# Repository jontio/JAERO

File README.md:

# JAERO

A SatCom ACARS demodulator and decoder for the Aero standard written in C++ Qt

This program demodulates and decodes ACARS messages sent from satellites to Aeroplanes (SatCom ACARS) commonly used when Aeroplanes are beyond VHF range. Demodulation is performed using the soundcard.
Such signals are typically around 1.5Ghz and can be received with a simple low gain antenna that can be home brewed in a few hours in conjunction with a cheap [RTL-SDR] dongle.

The 600 and 1200 bps SatCom ACARS signals are basically MSK like so the demodulator was forked from [JMSK]. The demodulator implements a coherent MSK demodulator type as seen at http://jontio.zapto.org/hda1/msk-demodulation2.html.

The 600 and 1200 bps demodulator uses the technique that treats the signal similar to [OQPSK] but with sine wave transitions rather than rectangular transitions. The BER (*Bit Error Rate*) versus EbNo (*Energy per bit to Noise power density*) performance in the presence of AWGN (*Additive White Gaussian Noise*) is the same as coherently demodulated differentially encoded [BPSK]. While designed for MSK it will also demodulate [GMSK] and some types of [BPSK]. The signal is supplied via the audio input of the computer’s soundcard.
The software implements differential decoding hence the modulator must use differential encoding. The output of the demodulator can be directed to either a built-in console or to a [UDP] network port.

An OQPSK demodulator was added and supports the faster 8400bps and 10.5k Aero signals.

Both 1200 and 10.5k burst C-band signal demodulation (From plane to ground station) are supported.

C-Channel signals at 8400bps that are for voice can be demodulated.

## Binaries

Precompiled binaries can be downloaded from [Releases].

## Directory structure

The [JAERO](JAERO) directory is where the Qt pro file is for the main application. The [udptextserver](udptextserver) directory is a small demo application for receiving data sent from JAERO.

## Compiling JAERO

Compiling JAERO requires the Qt framework. I would suggest using [MSYS2] to install the Qt framework and the rest of the development environment. Qt Creator can be used to compile JAERO and comes with the Qt framework. At least version 5 of the Qt framework is required. I only use MinGW and GCC for building so don't know if MSVC works.

I've now added Windows and Linux build scripts. The Windows build script requires MSYS2, once installed run msys64 clone the repo then type `./ci-windows-build.sh`. The Linux build script is for Debian based distros and will need to be changed for others; I have only tested it on some of the Ubuntu family (Ubuntu, Kubuntu and Lubuntu). For Linux type `./ci-linux-build.sh`, it will install JAERO as a few packages so uninstalling should be clean. For Windows there is no fancy installer but rather just a folder with the dependencies and the exe file itself. The build will fail if any of the dependency folders already exist; so the scripts could still do with a bit more work. Currently the aim of the scripts is as a way of automatically building JAERO from a default system so I can easily make changes to the code and not have the hassle of build releases.

I've added a continuous integration script [.github/workflows/ci-windows-build.yml](.github/workflows/ci-windows-build.yml) that will get Gihub to build JAERO for both Windows and Ubuntu. Currently the script is triggered manually in the [actions](https://github.com/jontio/JAERO/actions) tab. I suspect some older computers, say ones that don't support AVX instructions may now not run the new releases created in this manor and will need building on the intended computer itself.

JAERO's dependencies will undoubtedly change over time, so I suspect eventually the build scripts will fail and will need fixing. Till then they work, but I have no idea how long they will work for.

## Thanks

I'd like to thank everyone who has given their kind support for JAERO over the years. Thanks for Otti for getting the project started, John and Bev for setting up a worldwide large dish network, everyone who has donated, the people who have send feedback, people who use JAERO, Jeroen who done an excellent job programming new code for JAERO to bring some features that I’m sure will be appreciated by many, Tomasz for adding more ACARS message support, Corrosive for adding documentation, and the many other people who have written the libraries that JAERO uses.

Jonti 2021
<br>
https://jontio.zapto.org

[OQPSK]: https://en.wikipedia.org/wiki/Phase-shift_keying#Offset_QPSK_.28OQPSK.29
[GMSK]: https://en.wikipedia.org/wiki/Minimum-shift_keying#Gaussian_minimum-shift_keying
[BPSK]: https://en.wikipedia.org/wiki/Phase-shift_keying#Binary_phase-shift_keying_.28BPSK.29
[UDP]: https://en.wikipedia.org/wiki/User_Datagram_Protocol
[SSB]: https://en.wikipedia.org/wiki/Single-sideband_modulation
[Arduino]: https://www.arduino.cc/
[Varicode]: https://en.wikipedia.org/wiki/Varicode
[Spectrum Lab]: http://www.qsl.net/dl4yhf/spectra1.html
[JMSK]: https://github.com/jontio/JMSK
[RTL-SDR]: http://www.rtl-sdr.com/about-rtl-sdr/
[Releases]: https://github.com/jontio/JAERO/releases
[JAERO Wiki]: https://github.com/jontio/JAERO/wiki
[MSYS2]: https://www.msys2.org/

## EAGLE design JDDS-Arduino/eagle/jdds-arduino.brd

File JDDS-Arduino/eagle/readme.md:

Made with Eagle 7.4.0 Lite. (Free version)

These files show the default conntections for the JDDS-Arduino and a posible shield for an Arduino Uno.

With [Eagle PCB software](http://www.cadsoftusa.com/) You can modify the schematic and PCB to suit your needs.

Schematic of the connections

Possible shield for the Arduino Uno

Jonti

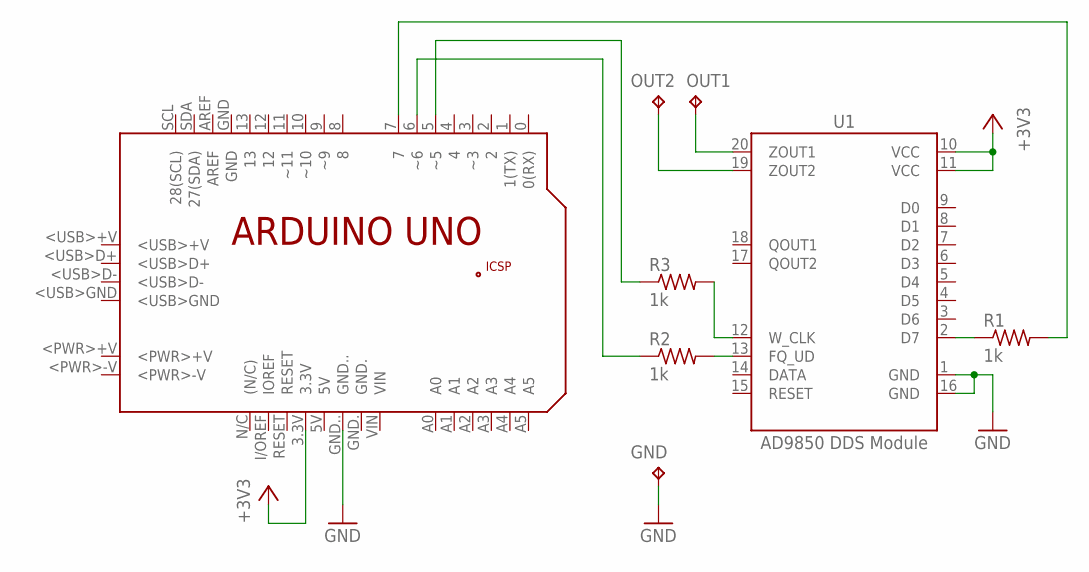
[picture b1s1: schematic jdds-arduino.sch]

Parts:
GND: TPPAD1-20; P1-20
OUT1, OUT2: TPPAD1-20; P1-20
PCB1: ARDUINO_UNO
R1, R2, R3: 1k; 0207/10
U1: AD9850 DDS Module; DDS_AD9850

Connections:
+3V3: PCB1.3.3V, U1.10 (VCC), U1.11 (VCC)
GND: GND.TP, PCB1.GND.., U1.1 (GND), U1.16 (GND)
unnamed: OUT1.TP, U1.20 (ZOUT1)
unnamed: OUT2.TP, U1.19 (ZOUT2)
unnamed: R1.1, U1.2 (D7)
unnamed: R2.2, U1.13 (FQ_UD)
unnamed: R3.2, U1.12 (W_CLK)
unnamed: PCB1.7, R1.2
unnamed: PCB1.5 (~5), R3.1
unnamed: PCB1.6 (~6), R2.1

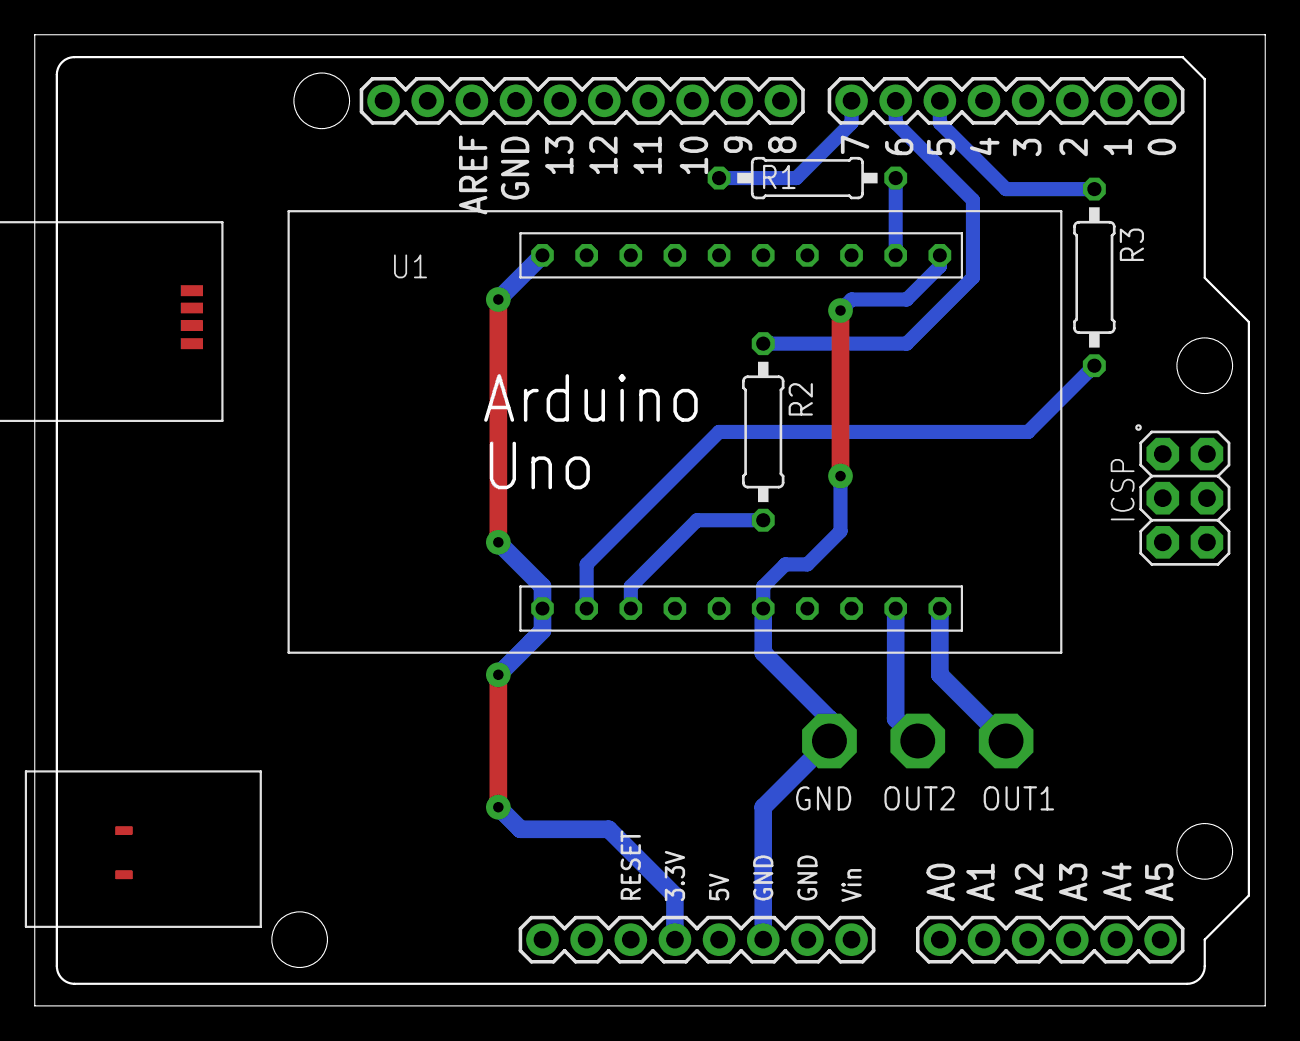
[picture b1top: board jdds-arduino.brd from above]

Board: 2 copper layers, 70.8 x 55.9 mm, 8 parts (0 on the bottom side), 10 nets.

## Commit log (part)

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2015-08-06 Inital push to github
2015-08-06 Test to see if I can push from Qt Creator
2015-08-06 test to see if qt creator can push
2015-08-06 3 try to push from qt
2015-08-06 Read me update
2015-08-06 Readme update
2015-08-06 UDP text server demo added
2015-09-06 Added an audio MSK modulator
2015-09-07 added min preamble time
2015-09-08 Added support for JDDS modulators
2015-09-09 Added Eagle CAD files for JDDS device
2015-09-09 Readme update for JDDS-Arduino
2015-09-10 Added beacon ability
2015-09-11 removed eg code, added scraping enable and text input persistence
2015-09-11 bug fix
2015-09-11 beacon bugfix
2015-11-17 binary literal workaround
2015-11-18 Missing ico file
2015-11-18 600 and 1200 baud
2015-11-18 tweak
2015-11-19 Added test device
2015-11-19 Fixed preamble detector
2015-11-19 First 16 bits displayed after UW
2015-11-20 Deinterleaver
2015-11-22 Viterbi algo, descrambler and delay lines
2015-11-22 Scrambler bug fixed and reset of scrambler done once per frame reather than twice
2015-11-24 Swapped bits, added SU type list
2015-11-25 Hide boring SUs and debug data, Fix short frame bug, add ascii for text SUs, add automatic switching between 600 and 1200 bps signals
2015-11-27 Defragmentation of 0x71 and SSUs and human readable output
2015-11-28 DCD added
2015-11-28 Different output formats added
2015-12-01 Added log window n things
2015-12-01 Rename JMSK.pro to JAERO.pro
2015-12-02 JDDS deleted
2015-12-02 rename folder
2015-12-02 tidy
2015-12-02 readme
2015-12-03 format 3
2015-12-04 ACARS defragmenter
2015-12-04 bandwidth selection
2015-12-04 version number correction
2015-12-06 log window update
2015-12-07 message scrollbar update
2015-12-08 Basic database plane lookup using csv file in format like http:// junzisun.com/aif/download does it
2015-12-08 wrong tab
2015-12-08 screenshot update
2015-12-10 addd database pane, database download button, reg and aes for url subs.
2015-12-12 log update, beep on text, downloader, misc
2015-12-13 Linux compatibility and beep sound as a resource
2015-12-13 Missing first char bug for log and format 3
2015-12-13 logwindow left right section linking better
2015-12-13 Linux desktop icon
2015-12-14 SQLite database for plane database
2015-12-14 sql minor fix
2015-12-15 UDP demo app freeze bug workaround
2015-12-18 version number changed in about message box
2015-12-18 Misc
2016-01-10 Support for 10.5k signals
2016-01-23 Repitition of data in top window and UDP output bug fixed
2016-01-25 Crash on AES lookup no match bug
2016-01-27 Spot beam frequency bug
2016-02-27 ADS parsing.UDP output for the bottom textedit. Removed unused code.
2016-03-03 SBS1 TCP server for outputting ADS positional information to third-party applications
2016-03-22 added dual channel 10.5k C-band burst demodulator, time check for sbs1 packets, concatinated sbs1 packets, and added timestamp to sbs1 packets.
2016-07-13 Added TCP client
2016-07-15 TCP ADS output button exclusion
2016-11-15 VRS server/client init bug fix
2016-12-31 use https for default csv database file
2017-03-26 GZIP decompression of database download
2017-08-17 issue #16 readme hash fix
2017-08-19 1200bps burst mode added soft FEC implemented for 10.5K burst
2017-08-19 minor changes
2017-08-20 minor updates
2017-08-20 adding libcorrect
2017-10-21 refactoring in progress
2017-10-22 minor updates, cleanup
2017-10-22 minor changes, cleanup
2017-10-22 changes to iir filter
2017-10-22 tuning the burst msk
2017-10-28 further changes
2017-10-31 further dev
2017-11-04 more changes
2017-11-11 symbol timing
2017-11-13 more 1200 bps burst changes. Works reasonably well now.
2017-11-14 removed old code
2017-11-16 soft fec for MSK non-burst mode
2017-11-17 burst MSK
2017-11-26 1200 bps burst
2017-11-26 rolling back some accidental commits
2017-11-26 1200 bps burst mode
2017-11-29 added a couple of sample files
2017-12-02 Cleaned up registry after clearing log
2017-12-03 removed the AFC condition in center freq changed
2017-12-27 tidying
2017-12-27 added static windows libcorrect libraries
2017-12-27 added windows shared libcorrect libraries
2017-12-27 changed burst MSK EBNO average time
2017-12-27 removed libcorrect archives, use dynamic linking
2017-12-29 added libcorrect source with inline popcnt function and 32 and 64 bit windows libraries. reduced signal threshold from 0.5 to 0.6.
2018-01-16 refactored using different symbol timing logic
2018-01-19 Revert "Dev"
2018-01-20 Minor fix. Added AES and GES check
2018-01-22 decreased frequency correction factor for MSK
2018-01-28 signed unsigned warning removal
2018-02-07 Added C channel processing
2018-02-10 tabs
2018-10-14 Flush log stream on every message
    Makes easier to follow the log file with tail.
2018-10-14 Support for decoding of ARINC uplink ATS applications via libacars library
2018-10-16 added window info tag as requested. added audio output device with dithering. added audio codec support.
2018-10-17 added mute button with persistance. fixed mkpath with empty string. changed libaeroambe to just an object so no need even for the headers.
2018-10-17 fixed libcorrect nameing in windows. added -lcorrect to linux. fixed unzipping of db files on linux (this needs unzip on linux now).
2018-10-18 reordering vorbis/ogg for static compiling. spelling mistake.
2018-10-20 audiooutdevice buffering changed to fix clock offsets. hopefully this is an improvment. changed mute to stop audiodevice out. added if no qobject library loaded then audiodevice is stoped.
2018-11-11 Linux install, KDE tested
2018-11-14 JAERO.pro: link with -lacars
2018-12-12 local include and win64 convenience bin for libacars for first stable release
2018-12-25 Switch to more generic libacars API, drop ARINC622-specific calls
    So far libacars was used to parse ARINC-622 ATS messages only. This
    patch causes all non-ADS-C messages to be passed to generic ACARS
    application decoding routine la_acars_decode_apps() which will decode
    any ACARS application supported by libacars (be it ARINC-622 or not).
2019-01-16 C channels work. Added 5000bw locking by default for 8400bps channels. 8400bps channels use a raised cosine weighting for locking. 8400bps channels use large complex fasrfir RRC filter b4 the mixer s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
2019-01-19 libacars update and 24000Hz bwl
2019-01-19 text update
2019-01-20 removed std::cout messages. fixed cchan assignment bug
2019-01-20 version and dynamically link libacars in windows
2019-04-22 fixed indentation
2019-04-23 added dcd check on preamble skip
2019-09-13 push b4 pull request merge
2019-09-14 PlaneLog::closeEvent changed to event->ignore();
2019-09-14 disable stupid deprecated-copy warnings cluttering up issues
2019-09-18 added c++11 to c++ flags
2019-10-07 multiple udp output sockets for bottom window. You put a space in between them. eg. "localhost:12345 192.168.1.22:4465"
2019-10-07 added tooltip for multiple udp output. added #define _USE_MATH_DEFINES needed for qt 5.13.1. changed about for next release tag.
2019-10-25 compiles with QMAKE_CXXFLAGS += '-Werror=format-security'. changed location of math constants define.
2021-03-10 add gitignore
2021-03-11 unbundled depenancies
2021-03-12 added samples. fixed 1200bps peak detection bug. still has a bug in the 8400 init locking that doesn't match kissfft
2021-03-14 added unit testing for replaced fft and fastfir classes
2021-03-14 added eol to gitignore
2021-03-14 start of windows ci
2021-03-14 ci test
2021-03-15 ci test update
2021-03-15 remove h files in matlab folder
2021-03-15 ci update
2021-03-16 make scripts exe
2021-03-16 jfft path
2021-03-16 del bak files
2021-03-16 how do i get this matrix thing working with msys2?
2021-03-16 ciupdate
2021-03-16 added ci badge to readme
2021-03-16 title version
2021-03-17 reset test
2021-03-18 removed downloader, added class enum shema but not using it yet
2021-03-18 removed comments and debug. changed times to utc
2021-03-18 added UTC appedded for times printed main form but not for log form. log form still shows UTC though
2021-03-18 settings ui tidy
2021-03-19 update log notes each acars msg
2021-03-19 added country model and type to log
2021-03-19 added test for planelog capacity
2021-03-20 added basestation links
2021-03-20 note
2021-03-20 ci wrong path
2021-03-20 db fallback path wrong
2021-03-20 ui date width
2021-03-21 removed 7za from window build. redeced artifact retention to 1 day
2021-07-20 Adding zeromq stuff
2021-07-21 removed some build artifacts
2021-07-21 revert pro file
2021-07-21 added qrc file
2021-07-21 winsock2 not on unix
2021-07-21 added libsodium to release
2021-07-21 Update .gitignore
    .qmake.cache and .qmake.stash need not be in root dir
2021-07-24 changed to QtConcurrent::run, fixed hanging bug in zmq receiver when closed if no source is available
2021-07-25 added bitrate message for zmq receiver. added to msk demodulator attempt to change samplerate depening on zmq bitrate message
2021-07-26 added zmq_audiosender class and removed the code that was doing the same thing in mainwindow (untested). tidy
2021-07-27 removed if statments from closeing audio
2021-07-29 zmq receiver changed from blocking to nonblocking
2021-08-06 chmod of pi-build.sh
2021-08-06 helper args passthrough for pi-build
2021-08-06 wrong version displayed on -v fixed
2021-08-07 added ability to disable planelog window for ppl who don't want the ram usage of it. added source to statusbar
2021-08-07 linked local audio decoding setting to mute to save CPU if needed. A bit of a patched solution but should be ok for most
2021-08-07 removed old commented out planelog window connections. these are now done depending on user settings
2021-08-08 version change for full release
2021-08-11 settings name added to titlebar if given
2021-09-30 Added JSON format output
2021-10-20 Revert "Added JSON format output"
2021-10-20 pull request merge. changed json to use qjsonobject. added db info. added arcars parse info.
2021-11-06 changes json output a bit and added more to the meta json output message
2021-11-06 forgot to set variables
2021-11-18 linux libacar2
2021-11-18 some windows mods for libacars2
2021-12-25 added missing libsqlite3-0.dll
2021-12-30 uniqueconnection for burst data
2021-12-30 Revert "uniqueconnection for burst data"
    This reverts commit 703862ec5800883b39d9bd97d5029d1b9586be80.
2022-02-06 windows build script to work on my computer
2022-02-06 added qmqtt module. fixed zmq checkbox bug
2022-02-11 added mqtt for the acars struct
2022-02-11 added qt5qmqtt.dll to windows build script
2022-02-11 linux build script update
2022-02-12 mqtt status LED
    add led function in mainwindow class for linking a label and led together and being able to hide both when set to disabled
    add change of connection state signal to MqttSubscriber
    connected the two together for the GUI to display what the state of the mqtt connection is when used
2022-03-12 mqtt requirment for pi reduced to 5.11
2022-03-13 pi script update to make work on my pi
2022-03-13 test to see why win build is failing
2022-03-13 win build failing is a windeployqt bug
2022-03-17 linux missing qt5-default package
2022-09-04 Do not abuse pulseaudio with single sample writes
    Prevent pulseaudio crashes, reduce CPU load.
2022-09-25 Free beep when not used
    Saves one audio stream per JAERO instance
2022-10-10 Adding JAERO and moc_predefs.h to gitignore
2022-10-10 Remove extraneous line
2022-10-11 Fix bug with src/dst
2022-10-12 Adding settings option for including a station ID in output JSON4
2022-10-23 Rename JSON4 to JSONdump
2022-10-31 Multiple outputs (#1)
    Add multiple feeder option
2022-11-02 Debugging CI
2022-11-02 More debugging
2022-11-02 Resolve issues with pcre deps
2022-11-29 removed linux build test units to avoid error: ‘turnOnNewDeleteOverloads’ is not a member of ‘MemoryLeakWarningPlugin’. this is just a temp solution
2022-11-29 version number change
2023-09-23 c channel frequency precision
2023-11-19 check for sublabel and strip if found
